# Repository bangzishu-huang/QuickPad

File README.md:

# QuickPad
A 5 key macro pad with a rotary encoder that is made in order to enhance productivity when working in documents (ex. copy and paste commands). There is a little extrusion on the top of the macropad, and it's intended for you to put a little figurine or anything of your choice on it (acts as a mini stand)!

I made this macropad in order to refresh my memory on schematic and also PCB design, as the last time I touched this was probably 1-2 months ago. I would say I learned a lot throughout the process and I really enjoyed it! Just in general, I feel like it was a really good project for me to get back into the groove with electronics, etc, so I'm looking forward to using this experience for more advanced future projects!

# Demo
This is an image of QuickPad and also my cat figure on the stand! (Just as how the design is intended to be used)

Image of QuickPad on it's own.

# 3D Model

# PCB
I used KiCAD for basically everything (schematic to pcb design). When I exported for gerbers I used the JLCPCB plugin!
(I didn't use a matrix layout as I had enough pins for all the features, if you are adding more keys or rotary encoders I suggest you use a matrix layout!)

- Schematic
- 
- PCB with zones
- 
- PCB without zones
- 

# QuickPad Case
I used AutoDesk Inventor in order to make the case of the macropad. The main reason I chose this was because I already had a lot of experience using this software. If you're a beginner to 3d modeling I would suggest learning and using Onshape, AutoDesk Fusion 360, or AutoDesk Inventor.

- The middle plate (or the top cover)
- 
- Bottom
- 

# Firmware
For QuickPad's firmware I used QMK. QuickPad contains the following features:
- VIA support
- RBG lighting (Pink)
- 5 keys to enhance productivity on documents
- Rotary Encoder for volume controll

(These can all be changed through qmk if needed)

# BOM (Bill of Materials)
Please keep in mind the case and rotary encoder knob are all 3d printed.

| Quantity | Material |
|---|---|
|1|Seeed XIAO RP2040|
|5|MX-Style Switches|
|5|White Blank DSA keycaps|
|5|SK6812 MINI-E LEDs|
|1|EC11 Rotary encoder|
|4|M3x16mm screws|

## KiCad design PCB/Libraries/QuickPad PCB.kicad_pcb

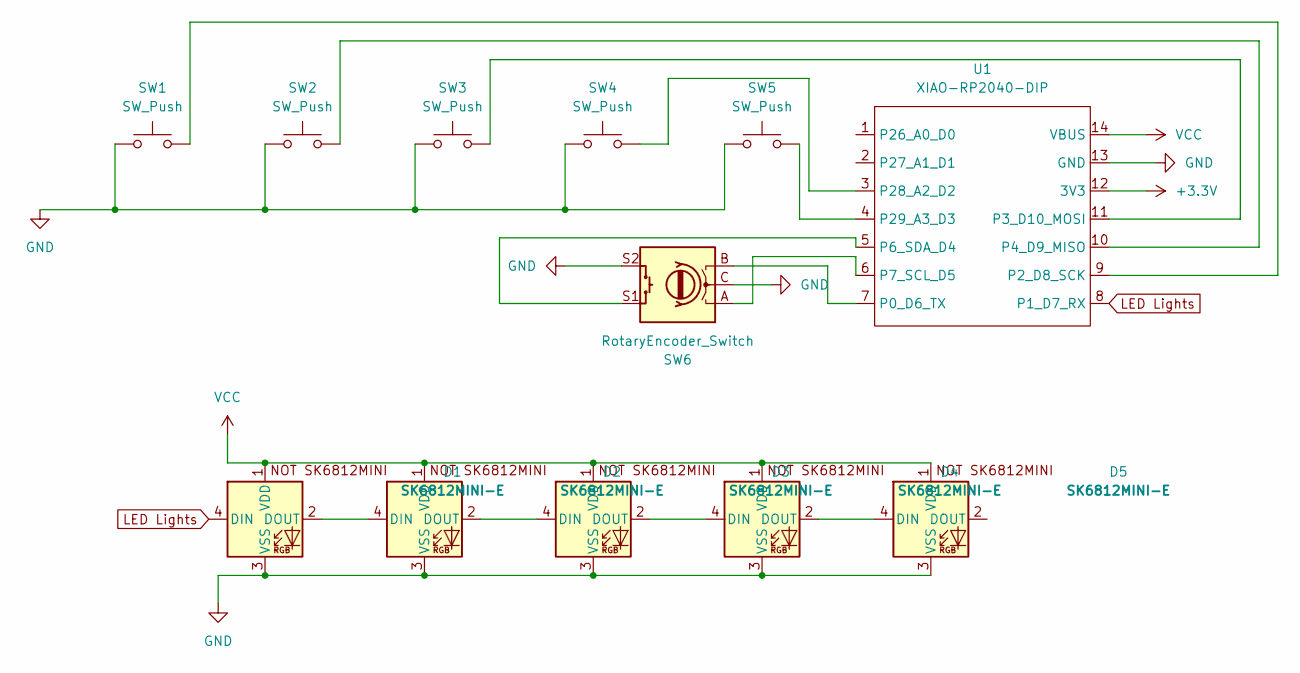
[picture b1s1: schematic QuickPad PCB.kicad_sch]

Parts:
D1, D2, D3, D4, D5: SK6812MINI-E; SK6812MINI-E_fixed
SW1, SW2, SW3, SW4, SW5: SW_Push; SW_Cherry_MX_1.00u_PCB
SW6: RotaryEncoder_Switch; RotaryEncoder_Alps_EC11E-Switch_Vertical_H20mm
U1: XIAO-RP2040-DIP

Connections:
+3.3V: U1.12 (3V3)
GND: D1.3 (VSS), D2.3 (VSS), D3.3 (VSS), D4.3 (VSS), D5.3 (VSS), SW1.1, SW2.1, SW3.1, SW4.1, SW5.1, SW6.C, SW6.S2, U1.13 (GND)
LED Lights: D1.4 (DIN), U1.8 (P1_D7_RX)
unnamed: D1.2 (DOUT), D2.4 (DIN)
unnamed: D2.2 (DOUT), D3.4 (DIN)
unnamed: D3.2 (DOUT), D4.4 (DIN)
unnamed: D4.2 (DOUT), D5.4 (DIN)
unnamed: SW6.B, U1.7 (P0_D6_TX)
unnamed: SW1.2, U1.9 (P2_D8_SCK)
unnamed: SW3.2, U1.11 (P3_D10_MOSI)
unnamed: SW2.2, U1.10 (P4_D9_MISO)
unnamed: SW6.S1, U1.5 (P6_SDA_D4)
unnamed: SW6.A, U1.6 (P7_SCL_D5)
unnamed: SW4.2, U1.3 (P28_A2_D2)
unnamed: SW5.2, U1.4 (P29_A3_D3)
VCC: D1.1 (VDD), D2.1 (VDD), D3.1 (VDD), D4.1 (VDD), D5.1 (VDD), U1.14 (VBUS)

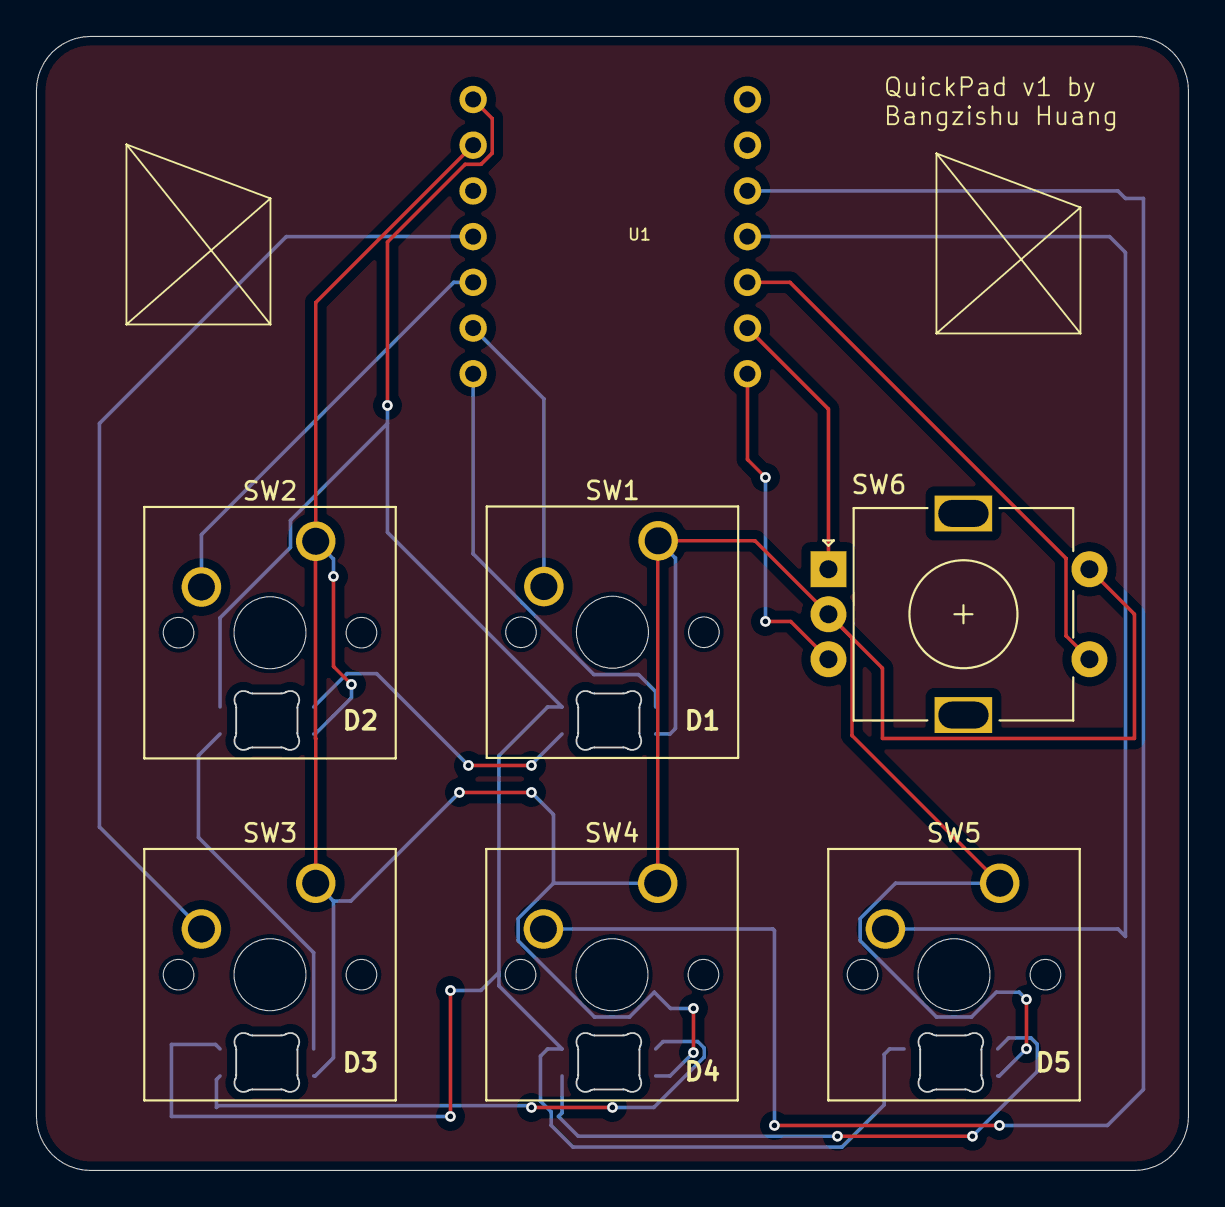
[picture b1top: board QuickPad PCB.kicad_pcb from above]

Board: 2 copper layers, 64.0 x 63.0 mm, 12 parts (1 on the bottom side), 15 nets.

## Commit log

2026-03-08 Add .DS_Store to gitignore
2026-03-08 Added PCB and STEP files
2026-03-08 Enhance README with project details and personal reflections
    Expanded project description to include additional features and personal insights.
2026-03-08 Finished and added firmware
2026-03-08 added gerbers to production
2026-03-08 Expand README with PCB, case, firmware, and BOM details
    Added detailed sections on PCB design, case construction, firmware features, and BOM for the macropad project.
2026-03-08 Update keycap color from Pink to White
2026-03-29 added demo images
2026-03-29 Enhance README with demo images and 3D model
    Added demo images and 3D model section to README.
2026-03-29 organized demo files
